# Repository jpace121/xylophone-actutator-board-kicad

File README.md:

# Xylophone Actuator Board #

KiCad files for the Actuator Board for my robotic xylophone project.
The actuator holds the RGB LEDs and the solenoids, with the corresponding
interface circuits to the Micrcontroller. The is connected to these
components using ribbon cable and its own "shield", whose CAD files
will be in a yet to be created repository.

Any software is dual licensed Apache 2.0/MIT.

All other files are licensed
[CC BY 4.0](https://creativecommons.org/licenses/by/4.0/).

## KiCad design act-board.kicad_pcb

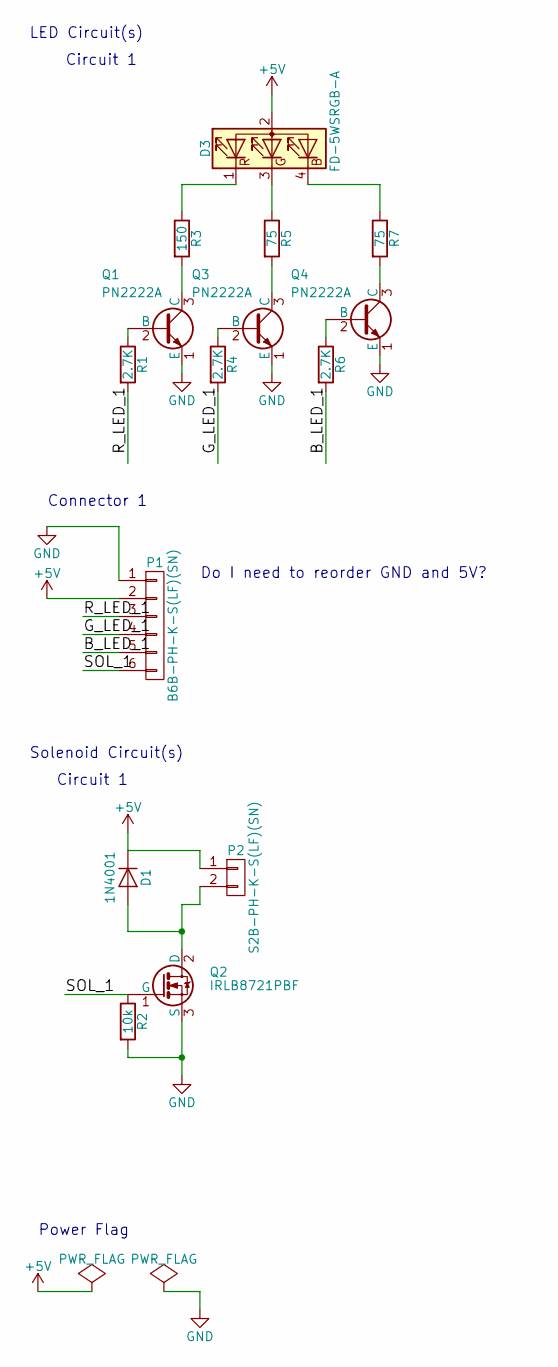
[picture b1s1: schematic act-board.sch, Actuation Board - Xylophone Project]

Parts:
D1: 1N4001; Diode_DO-35_SOD27_Horizontal_RM10
D3: FD-5WSRGB-A; LED_D5.0mm-4
P1: B6B-PH-K-S(LF)(SN); JST_PH_B6B-PH-K_06x2.00mm_Straight
P2: S2B-PH-K-S(LF)(SN); JST_PH_S2B-PH-K_02x2.00mm_Angled
Q1, Q3, Q4: PN2222A; TO-92_Inline_Narrow_Oval
Q2: IRLB8721PBF; TO-220_Neutral123_Vertical_LargePads
R1, R4, R6: 2.7K; Resistor_Horizontal_RM7mm
R2: 10k; Resistor_Horizontal_RM7mm
R3: 150; Resistor_Horizontal_RM7mm
R5, R7: 75; Resistor_Horizontal_RM7mm

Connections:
+5V: D1.1 (K), D3.2 (A), P1.2, P2.1
/B_LED_1: P1.5, R6.2
/G_LED_1: P1.4, R4.2
/R_LED_1: P1.3, R1.2
/SOL_1: P1.6, Q2.1 (G), R2.1
GND: P1.1, Q1.1 (E), Q2.3 (S), Q3.1 (E), Q4.1 (E), R2.2
unnamed: D1.2 (A), P2.2, Q2.2 (D)
unnamed: D3.1 (RK), R3.1
unnamed: D3.3 (GK), R5.1
unnamed: D3.4 (BK), R7.1
unnamed: Q1.2 (B), R1.1
unnamed: Q1.3 (C), R3.2
unnamed: Q3.2 (B), R4.1
unnamed: Q3.3 (C), R5.2
unnamed: Q4.2 (B), R6.1
unnamed: Q4.3 (C), R7.2

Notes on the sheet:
LED Circuit(s)
Circuit 1
Solenoid Circuit(s)
Circuit 1
Do I need to reorder GND and 5V?
Power Flag
Connector 1

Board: 2 copper layers, 15 parts (0 on the bottom side), 16 nets, no tracks yet.

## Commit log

2017-01-08 Initial commit.
    Try to lay out one of 8 circuits.
    RGB LED footprint messed up.
2017-02-12 Fix RGB LED pad.
